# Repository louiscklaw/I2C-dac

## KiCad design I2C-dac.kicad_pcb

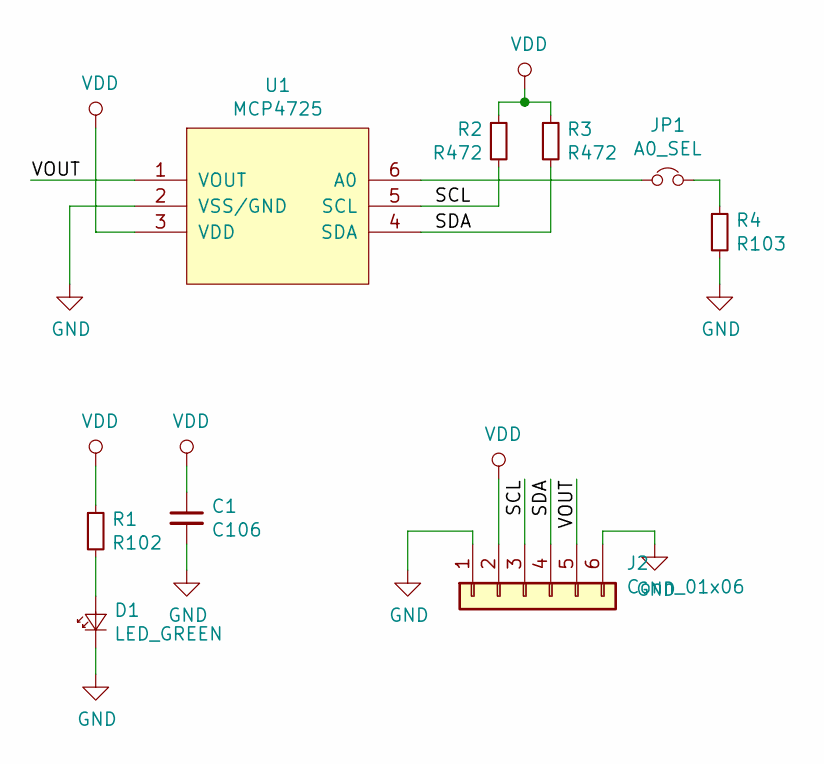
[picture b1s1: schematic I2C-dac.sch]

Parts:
C1: C106; C_0805_2012Metric_Pad1.15x1.40mm_HandSolder
D1: LED_GREEN; LED_0805_2012Metric_Castellated
J2: Conn_01x06; PinHeader_1x06_P2.54mm_Vertical
JP1: A0_SEL; SolderJumper-2_P1.3mm_Bridged_RoundedPad1.0x1.5mm
R1: R102; R_0805_2012Metric_Pad1.15x1.40mm_HandSolder
R2, R3: R472; R_0805_2012Metric_Pad1.15x1.40mm_HandSolder
R4: R103; R_0805_2012Metric_Pad1.15x1.40mm_HandSolder
U1: MCP4725; SOT-23-6_Handsoldering

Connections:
/SCL: J2.3, R2.2, U1.5 (SCL)
/SDA: J2.4, R3.2, U1.4 (SDA)
/VOUT: J2.5, U1.1 (VOUT)
GND: C1.2, D1.1 (K), J2.1, J2.6, R4.2, U1.2 (VSS/GND)
unnamed: D1.2 (A), R1.2
unnamed: JP1.1, U1.6 (A0)
unnamed: JP1.2, R4.1
VDD: C1.1, J2.2, R1.1, R2.1, R3.1, U1.3 (VDD)

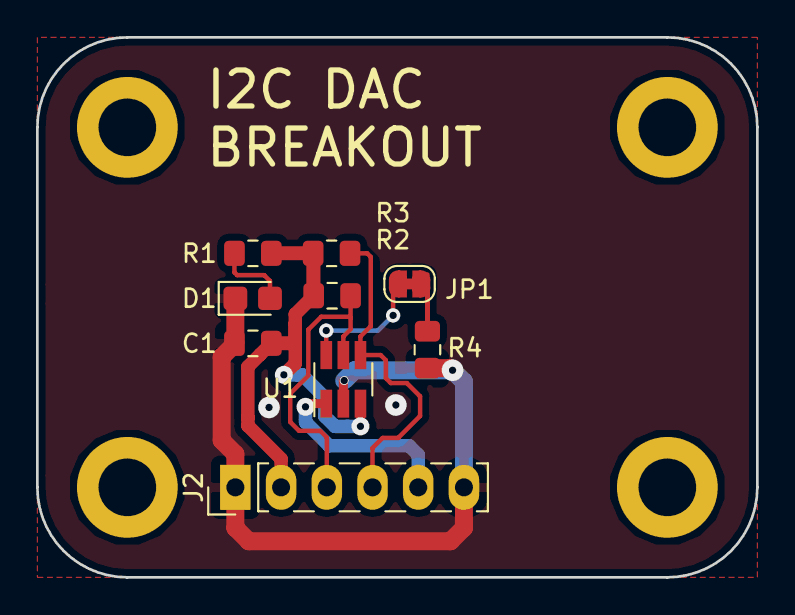
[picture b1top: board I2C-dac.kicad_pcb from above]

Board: 2 copper layers, 40.0 x 30.0 mm, 9 parts (0 on the bottom side), 8 nets.

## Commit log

2018-10-18 update,
2020-05-05 ci: init travis build config,
2020-05-05 ci: init travis token,
